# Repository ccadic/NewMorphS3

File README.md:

# NewMorphS3
New ESP32S3 dev board from Morpheans.com 

PSP32-S3 game station version 2:  display position modified + I2S sound added + accelerometer added + uSD Card added - Still USB-C, Battery , Charger, ON/OFF Slider switch , PSP joystick and 2 buttons. 

From @sulfuroid

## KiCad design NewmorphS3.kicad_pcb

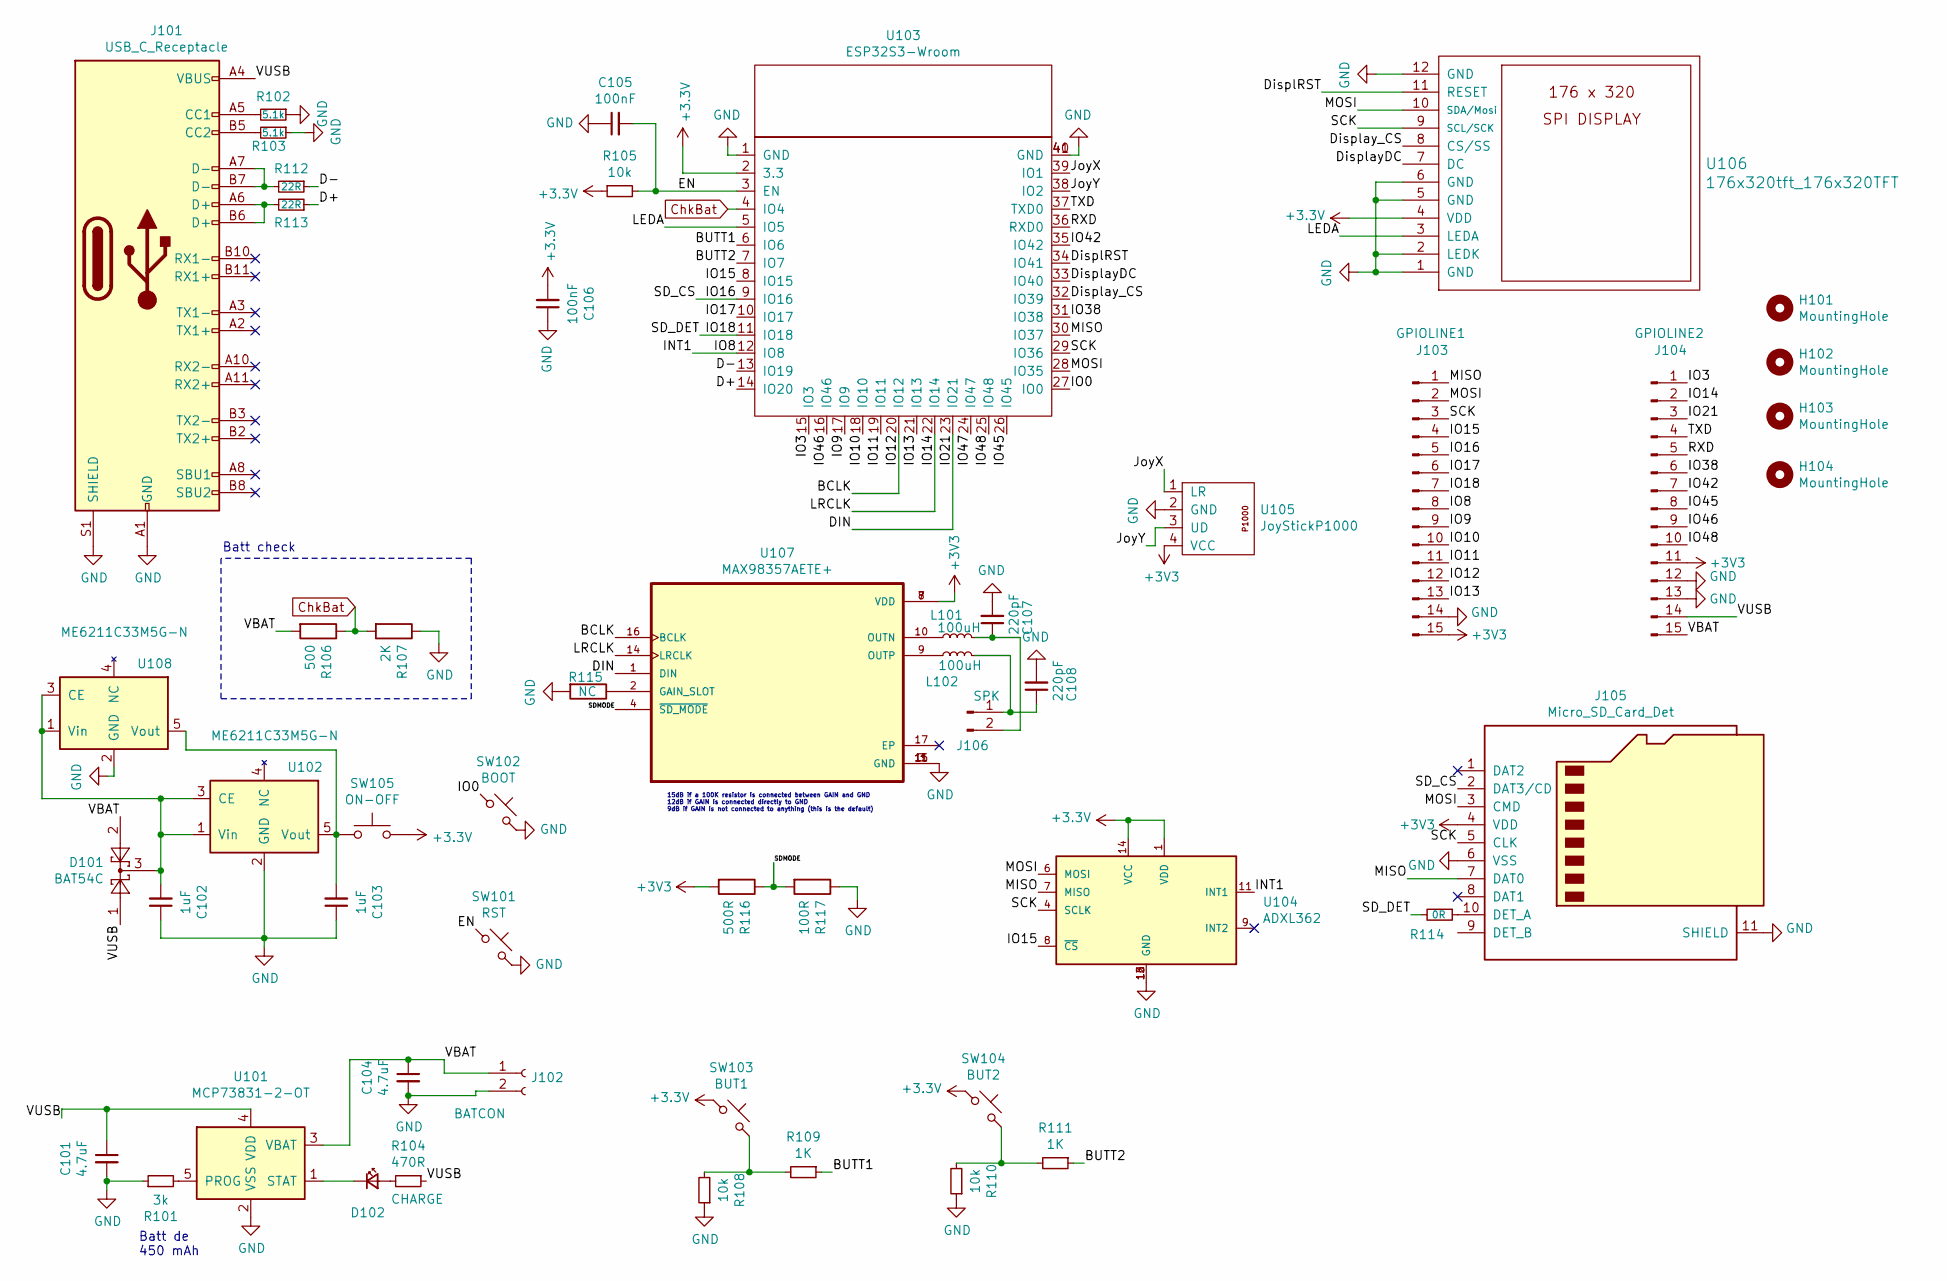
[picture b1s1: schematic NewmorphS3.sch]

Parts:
C101, C104: 4.7uF; C_0603_1608Metric
C102, C103: 1uF; C_0603_1608Metric
C105: 100nF; C_0805_2012Metric_Pad1.18x1.45mm_HandSolder
C106: 100nF; C_0603_1608Metric
C107, C108: 220pF; C_0603_1608Metric
D101: BAT54C; SOT-23
D102: CHARGE; LED_0603_1608Metric
H101, H102, H103, H104: MountingHole; MountingHole_2.2mm_M2_Pad_Via
J101: USB_C_Receptacle; GT-USB-7010
J102: BATCON; JST_PH_S2B-PH-SM4-TB_1x02-1MP_P2.00mm_Horizontal
J103: GPIOLINE1; PinHeader_1x15_P2.54mm_Vertical
J104: GPIOLINE2; PinHeader_1x15_P2.54mm_Vertical
J105: Micro_SD_Card_Det; microSD_HC_Molex_104031-0811
J106: SPK; 2pads
L101, L102: 100uH; L_0805_2012Metric
R101: 3k; R_0603_1608Metric
R102, R103: 5.1k; R_0603_1608Metric
R104: 470R; R_0603_1608Metric
R105: 10k; R_0805_2012Metric_Pad1.20x1.40mm_HandSolder
R106: 500; R_0603_1608Metric
R107: 2K; R_0603_1608Metric
R108, R110: 10k; R_0603_1608Metric
R109, R111: 1K; R_0603_1608Metric
R112, R113: 22R; R_0603_1608Metric
R114: 0R; R_0603_1608Metric
R115: NC; R_0603_1608Metric
R116: 500R; R_0603_1608Metric
R117: 100R; R_0603_1608Metric
SW101: RST; SKRPABE010
SW102: BOOT; SKRPABE010
SW103: BUT1; SW_TP1003
SW104: BUT2; SW_TP1003
SW105: ON-OFF; SW_SPDT_PCM12
U101: MCP73831-2-OT; SOT-23-5
U102, U108: ME6211C33M5G-N; SOT-23-5
U103: ESP32S3-Wroom; ESP32-S3-wrooom
U104: ADXL362; DIGIKEY ADXL362BCCZ-RL7CT-ND
U105: JoyStickP1000; JoystickP1000
U106: 176x320tft_176x320TFT; ST7789-176x320
U107: MAX98357AETE+; QFN50P300X300X80-17N

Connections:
/BCLK: J103.12, U103.20 (IO12), U107.16 (BCLK)
/BUTT1: R109.1, U103.6 (IO6)
/BUTT2: R111.1, U103.7 (IO7)
/D+: R113.1, U103.14 (IO20)
/D-: R112.1, U103.13 (IO19)
/DIN: J104.3, U103.23 (IO21), U107.1 (DIN)
/DisplRST: U103.34 (IO41), U106.11 (RESET)
/DisplayDC: U103.33 (IO40), U106.7 (DC)
/Display_CS: U103.32 (IO39), U106.8 (CS/SS)
/EN: C105.2, R105.2, SW101.1, U103.3 (EN)
/INT1: J103.8, U103.12 (IO8), U104.11 (INT1)
/IO0: SW102.1, U103.27 (IO0)
/IO3: J104.1, U103.15 (IO3)
/IO9: J103.9, U103.17 (IO9)
/IO10: J103.10, U103.18 (IO10)
/IO11: J103.11, U103.19 (IO11)
/IO13: J103.13, U103.21 (IO13)
/IO14: J104.2, U103.22 (IO14), U107.14 (LRCLK)
/IO15: J103.4, U103.8 (IO15), U104.8 (~CS)
/IO16: J103.5, J105.2 (DAT3/CD), U103.9 (IO16)
/IO17: J103.6, U103.10 (IO17)
/IO18: J103.7, R114.2, U103.11 (IO18)
/IO38: J104.6, U103.31 (IO38)
/IO42: J104.7, U103.35 (IO42)
/IO45: J104.8, U103.26 (IO45)
/IO46: J104.9, U103.16 (IO46)
/IO48: J104.10, U103.25 (IO48)
/JoyX: U103.39 (IO1), U105.1 (LR)
/JoyY: U103.38 (IO2), U105.3 (UD)
/LEDA: U103.5 (IO5), U106.3 (LEDA)
/MISO: J103.1, J105.7 (DAT0), U103.30 (IO37), U104.7 (MISO)
/MOSI: J103.2, J105.3 (CMD), U103.28 (IO35), U104.6 (MOSI), U106.10 (SDA/Mosi)
/RXD: J104.5, U103.36 (RXD0)
/SCK: J103.3, J105.5 (CLK), U103.29 (IO36), U104.4 (SCLK), U106.9 (SCL/SCK)
/SDMODE: R116.1, R117.2, U107.4 (~SD_MODE)
/TXD: J104.4, U103.37 (TXD0)
/VBAT: C104.1, D101.2, J102.1, J104.15, R106.2, U101.3 (VBAT)
/VUSB: C101.1, D101.1, J101.A4 (VBUS), J101.A9 (VBUS), J101.B4 (VBUS), J101.B9 (VBUS), J104.14, R104.1, U101.4 (VDD)
ChkBat: R106.1, R107.2, U103.4 (IO4)
GND: C101.2, C102.1, C103.1, C104.2, C105.1, C106.1, C107.2, C108.2, J101.A1 (GND), J101.A12 (GND), J101.B1 (GND), J101.B12 (GND), J101.S1 (SHIELD), J102.2, J103.14, J104.12, J104.13, J105.6 (VSS), J105.11 (SHIELD), R101.1, R102.1, R103.1, R107.1, R108.1, R110.1, R115.2, R117.1, SW101.2, SW102.2, U101.2 (VSS), U102.2 (GND), U103.1 (GND), U103.40 (GND), U103.41 (GND), U104.12 (GND), U104.13 (GND), U104.16 (GND), U105.2 (GND), U106.1 (GND), U106.2 (LEDK), U106.5 (GND), U106.6 (GND), U106.12 (GND), U107.3 (GND), U107.11 (GND), U107.15 (GND), U108.2 (GND)
unnamed: C102.2, D101.3, U102.1 (Vin), U102.3 (CE), U108.1 (Vin), U108.3 (CE)
unnamed: C103.2, SW105.1, U102.5 (Vout), U108.5 (Vout)
unnamed: C107.1, J106.2, L101.2
unnamed: C108.1, J106.1, L102.2
unnamed: D102.1 (K), U101.1 (STAT)
unnamed: D102.2 (A), R104.2
unnamed: J101.A5 (CC1), R102.2
unnamed: J101.A6 (D+), J101.B6 (D+), R113.2
unnamed: J101.A7 (D-), J101.B7 (D-), R112.2
unnamed: J101.B5 (CC2), R103.2
unnamed: J105.10 (DET_A), R114.1
unnamed: L101.1, U107.10 (OUTN)
unnamed: L102.1, U107.9 (OUTP)
unnamed: R101.2, U101.5 (PROG)
unnamed: R108.2, R109.2, SW103.2
unnamed: R110.2, R111.2, SW104.2
unnamed: R115.1, U107.2 (GAIN_SLOT)

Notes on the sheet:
Batt de 450 mAh
Batt check
15dB if a 100K resistor is connected between GAIN and GND 12dB if GAIN is connected directly to GND 9dB if GAIN is not connected to anything (this is the default)

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
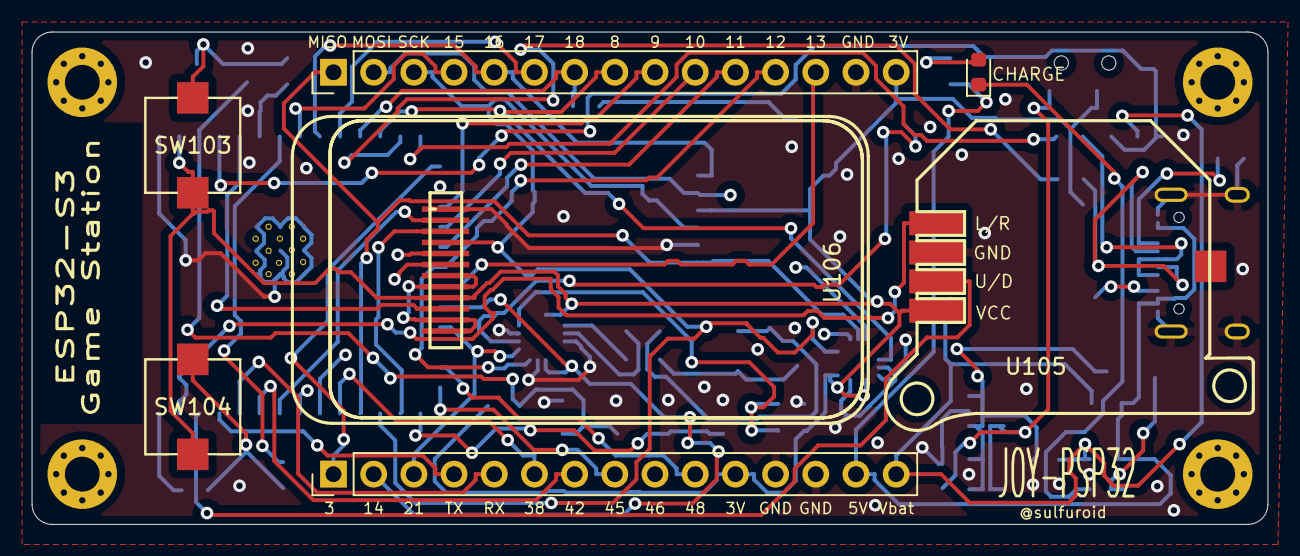
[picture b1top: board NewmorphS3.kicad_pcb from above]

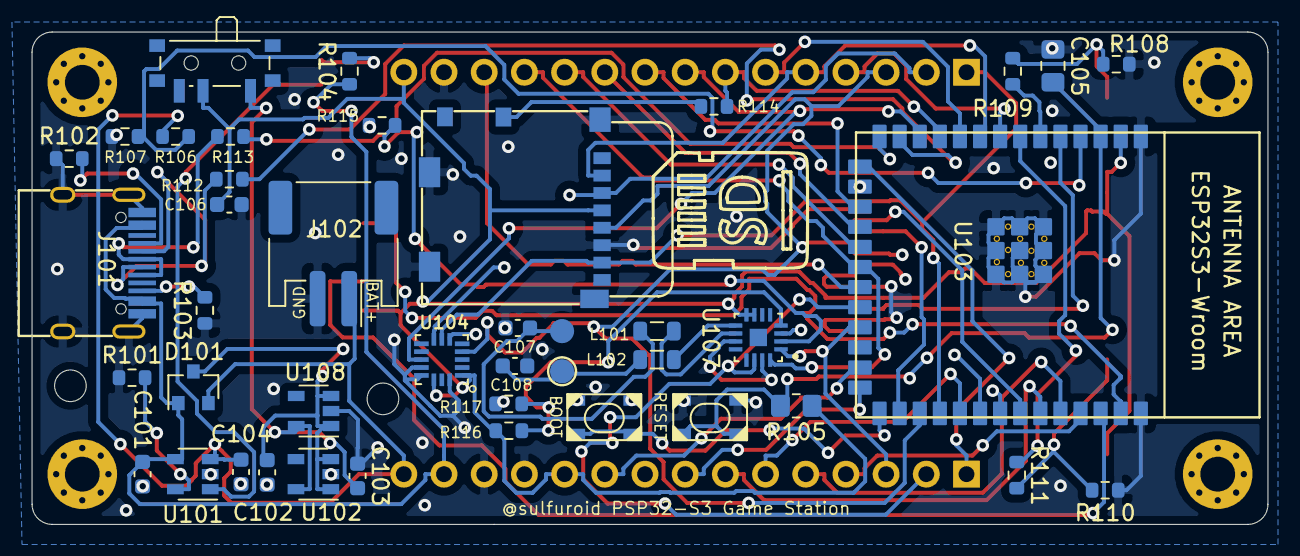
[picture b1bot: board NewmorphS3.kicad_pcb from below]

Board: 4 copper layers, 78.1 x 31.1 mm, 52 parts (41 on the bottom side), 58 nets.
